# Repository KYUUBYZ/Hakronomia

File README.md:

# Hakronomia

<!--START_SECTION:BOM-TABLE-->
| Item | Qty | Supplier | Cost/item | Total Cost | link |
| --- | --- | --- | --- | --- | --- |
| 0.1uF | 6 | Unikeyic | $0.08 | $0.48 | [Link](https://www.unikeyic.com/products/ceramic-capacitors/gcd21br72a104ka01l/10036938.html?sku=1003001027405269) |
| 2.2nF | 2 | Unikeyic | $0.05 | $0.10 | [Link](https://www.unikeyic.com/products/ceramic-capacitors/gcm2165c2a222ja16d/5775567.html?sku=1003001445194783) |
| 10nF | 6 | Unikeyic | $0.01 | $0.06 | [Link](https://www.unikeyic.com/products/ceramic-capacitors/cc0805jrx7r9bb103/17962920.html?sku=1003001445184833) |
| 2.2uF | 2 | Unikeyic | $0.05 | $0.10 | [Link](https://www.unikeyic.com/products/ceramic-capacitors/cga4j3x7r1c225kt0y0n/8873476.html?sku=1003001017784221) |
| 10uF | 4 | Unikeyic | $0.08 | $0.32 | [Link](https://www.unikeyic.com/products/ceramic-capacitors/c2012x7r0j106k125ab/17422021.html?sku=1003001013214412) |
| AudioJack5 | 1 | Futuranet | $0.30 | $0.30 | [Link](https://futuranet.it/prodotto/presa-jack-stereo-35-mm-da-circuito-stampato/) |
| 330R | 12 | Unikeyic | $0.01 | $0.12 | [Link](https://www.unikeyic.com/products/surface-mount-resistors/rc0805fr-07330rl/4454264.html?sku=1003001443534963) |
| 4.7k | 2 | Unikeyic | $0.01 | $0.02 | [Link](https://www.unikeyic.com/products/surface-mount-resistors/rc0805fr-7w4k7l/3329266.html?sku=1003001021096266) |
| 75k | 1 | Unikeyic | $0.00 | $0.00 | [Link](https://www.unikeyic.com/products/surface-mount-resistors/wr08x753-jtl/28917829.html?sku=1003001442043903) |
| 10k | 2 | Unikeyic | $0.00 | $0.00 | [Link](https://www.unikeyic.com/products/surface-mount-resistors/0805w8f1002t5e/33861683.html?sku=1003001012328856) |
| 470R | 2 | Unikeyic | $0.00 | $0.00 | [Link](https://www.unikeyic.com/products/surface-mount-resistors/0805w8f4700t5e/27378691.html?sku=1003001012328951) |
| 0R | 1 | Unikeyic | $0.01 | $0.01 | [Link](https://www.unikeyic.com/products/surface-mount-resistors/rtt050000ftp/30082103.html?sku=1003001013772933) |
| RP2040-Zero | 1 | Futuranet | $6.61 | $6.61 | [Link](https://futuranet.it/prodotto/scheda-di-sviluppo-mini-basata-su-rp2040/) |
| RotaryEncoder_Switch_MP | 3 | Unikeyic | $1.49 | $4.47 | [Link](https://www.unikeyic.com/products/encoders-and-decoders/ec11e15244g1/24342867.html?sku=1003001012811431) |
| ER_OLEDM0.91_1x-I2C | 1 | Futuranet | $6.50 | $6.50 | [Link](https://futuranet.it/prodotto/display-oled-i2c-091-128x32-pixel/) |
| MPR121QR2 | 1 | Unikeyic | $1.61 | $1.61 | [Link](https://www.unikeyic.com/products/other-interface/mpr121qr2/11118659.html?sku=1003001027325782) |
| PCM5102A | 1 | Unikeyic | $1.31 | $1.31 | [Link](https://www.unikeyic.com/products/adc-dac-specialized/pcm5102apwr/33225117.html?sku=1003001444976630) |
| Estimated total shipping | 1 |  |  | $7.50 |  |
<!--END_SECTION:BOM-TABLE-->
# HOW TO INSTALL THE FIRMWARE (Hakronomia.py):

1)    Connect your RP2040-ZERO to your PC using a data transfer cable while pressing BOOT 

2)    Install/Copy the "adafruit-ciruitpython-waveshare" file i put in this folder ON the RP2040-ZERO.

3)    you should see file be downloaded on your microcontroller.

4)    From CircuitPython libraries bundle, copy "adafruit_mpr121, adafruit_displayio_ssd1306, adafruit_display_text, adafruit_bus_device" on the rp2040-zero.

5)    Copy Hakronomia.py on the rp2040-zero

# What is Hakronomia?
Hakronomia, Midi keyboard, it's a Piano style keyboard an it has 12 exposed copper plates keys, plus 3 rotary encoder, a 0.91 inch screen, a switch and a 3.5mm AudioJack.
It uses a MPR121QR2 ( The MPR121QR2 is a Capacitive Touch Sensor Controller )  and the PCM5102A ( DAC Chip (Digital-to-Analog Converter ).

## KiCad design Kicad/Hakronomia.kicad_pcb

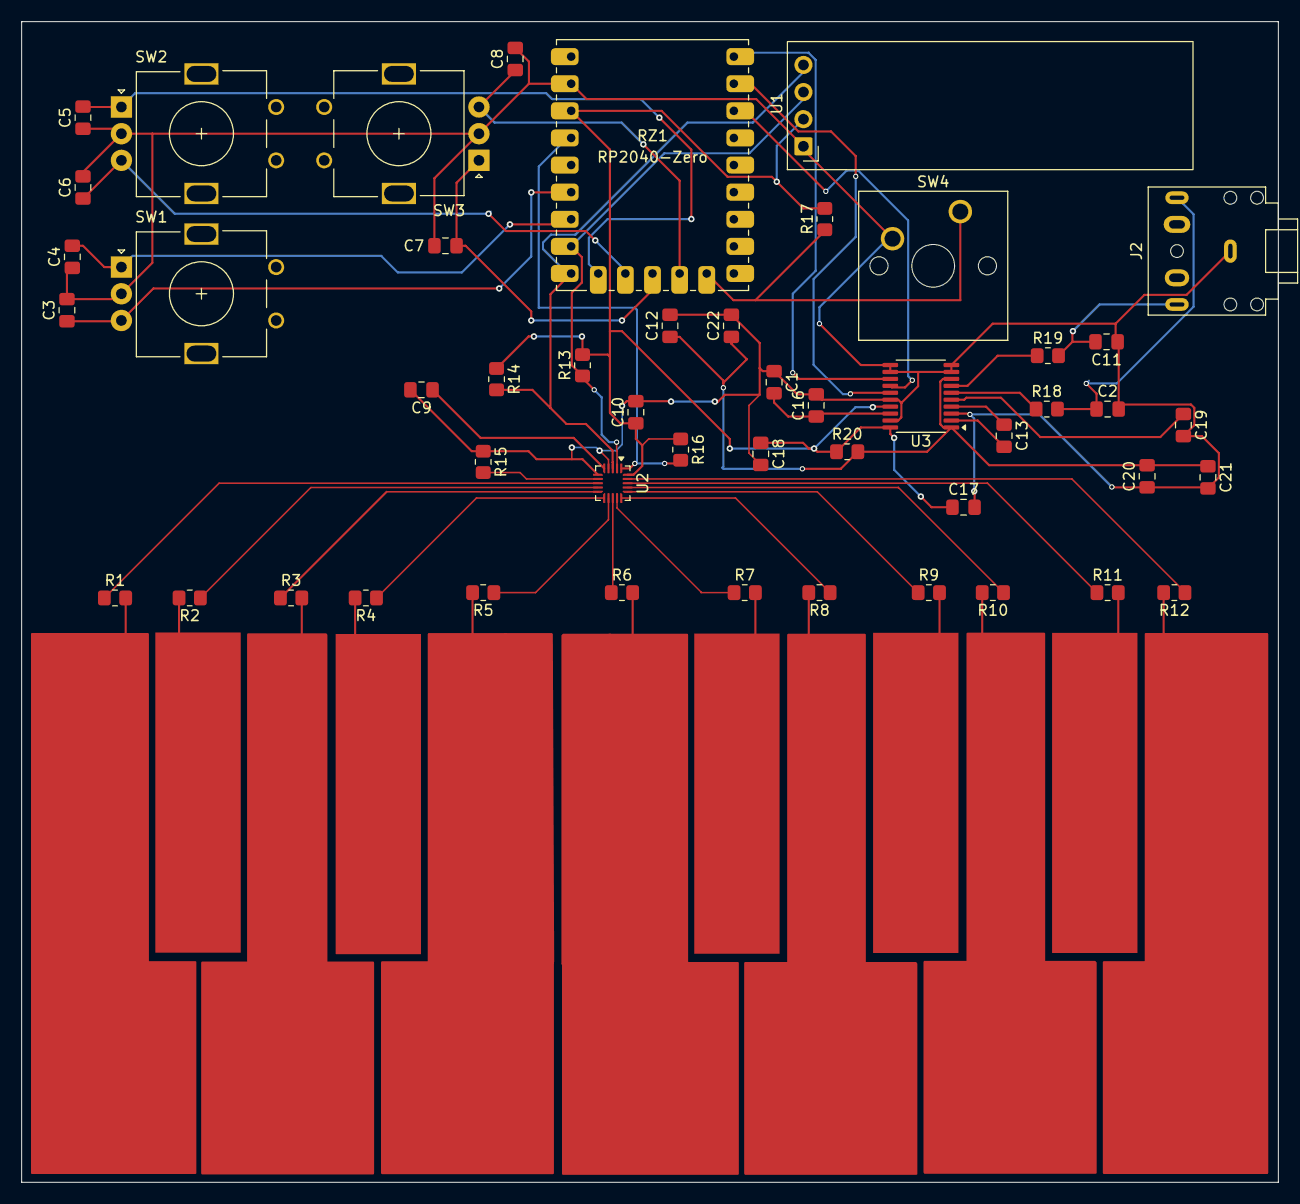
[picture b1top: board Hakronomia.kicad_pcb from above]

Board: 2 copper layers, 117.8 x 108.8 mm, 50 parts (0 on the bottom side), 50 nets.

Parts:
C1, C9, C10, C12, C18, C20: 0.1uF; C_0805_2012Metric_Pad1.18x1.45mm_HandSolder
C2, C11: 2.2nF; C_0805_2012Metric_Pad1.18x1.45mm_HandSolder
C3, C4, C5, C6, C7, C8: 10nF; C_0805_2012Metric_Pad1.18x1.45mm_HandSolder
C13, C19: 2.2uF; C_0805_2012Metric_Pad1.18x1.45mm_HandSolder
C16, C17, C21, C22: 10uF; C_0805_2012Metric_Pad1.18x1.45mm_HandSolder
J1: Conn_01x12_Pin; Hakronomia Pads
J2: AudioJack5; Jack_3.5mm_CUI_SJ1-3525N_Horizontal
R1, R2, R3, R4, R5, R6, R7, R8, R9, R10, R11, R12: 330R; R_0805_2012Metric_Pad1.20x1.40mm_HandSolder
R13, R14: 4.7k; R_0805_2012Metric_Pad1.20x1.40mm_HandSolder
R15: 75k; R_0805_2012Metric_Pad1.20x1.40mm_HandSolder
R16, R17: 10k; R_0805_2012Metric_Pad1.20x1.40mm_HandSolder
R18, R19: 470R; R_0805_2012Metric_Pad1.20x1.40mm_HandSolder
R20: 0R; R_0805_2012Metric_Pad1.20x1.40mm_HandSolder
RZ1: RP2040-Zero
SW1, SW2, SW3: RotaryEncoder_Switch_MP; RotaryEncoder_Alps_EC11E_Vertical_H20mm
SW4: SW_Push; SW_Cherry_MX_1.25u_PCB
U1: ER_OLEDM0.91_1x-I2C
U2: MPR121QR2; UQFN-20_3x3mm_P0.4mm
U3: PCM5102A; TSSOP-20_4.4x6.5mm_P0.65mm

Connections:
AGND: C1.1, C2.2, C3.2, C4.1, C5.1, C6.2, C7.1, C8.2, C9.2, C10.2, C11.1, C12.2, C16.2, C17.2, C18.2, C19.2, C20.1, C21.2, C22.2, J2.S, R15.1, RZ1.22 (GND), SW1.C, SW2.C, SW3.C, SW4.2, U1.1 (GND), U2.4 (ADDR), U2.6 (VSS), U3.3 (CPGND), U3.9 (AGND), U3.10 (DEMP), U3.11 (FLT), U3.12 (SCK), U3.16 (FMT), U3.19 (DGND)
AVDD: C12.1, C20.2, C21.1, C22.1, R20.2, U3.1 (CPVDD), U3.8 (AVDD)
BCK: RZ1.1 (GP0), U3.13 (BCK)
DIN: RZ1.3 (GP2), U3.14 (DIN)
DVDD: C10.1, C17.1, C18.1, R13.2, R14.1, R16.1, R17.2, R20.1, RZ1.21 (3V3), U1.2 (VCC), U2.20 (VDD), U3.17 (XSMT), U3.20 (DVDD)
ENC-A0: C4.2, RZ1.17 (GP26), SW1.A
ENC-A1: C5.2, RZ1.14 (GP13), SW2.A
ENC-A2: C7.2, RZ1.12 (GP11), SW3.A
ENC-B0: C3.1, RZ1.18 (GP27), SW1.B
ENC-B1: C6.1, RZ1.13 (GP12), SW2.B
ENC-B2: C8.1, RZ1.11 (GP10), SW3.B
LRCK: RZ1.2 (GP1), U3.15 (LRCK)
MPR-IRQ: R16.2, RZ1.20 (GP29), U2.1 (~IRQ)
unnamed: C2.1, J2.T, R18.2
unnamed: C11.2, J2.R, R19.2
unnamed: J1.1, R1.2
unnamed: J1.2, R2.2
unnamed: J1.3, R3.2
unnamed: J1.4, R4.2
unnamed: J1.5, R5.2
unnamed: J1.6, R6.2
unnamed: J1.7, R7.2
unnamed: J1.8, R8.2
unnamed: J1.9, R9.2
unnamed: J1.10, R10.2
unnamed: J1.11, R11.2
unnamed: J1.12, R12.2
unnamed: R15.2, U2.7 (REXT)
unnamed: C9.1, U2.5 (VREG)
unnamed: C13.1, U3.4 (CAPM)
unnamed: C13.2, U3.2 (CAPP)
unnamed: C1.2, C16.1, U3.18 (LDOO)
unnamed: R18.1, U3.6 (OUTL)
unnamed: R19.1, U3.7 (OUTR)
SCL: R13.1, RZ1.16 (GP15), U1.3 (SCL), U2.2 (SCL)
SDA: R14.2, RZ1.15 (GP14), U1.4 (SDA), U2.3 (SDA)
SWITCH-0: R17.1, RZ1.10 (GP9), SW4.1
Touch1: R1.1, U2.8 (ELE0)
Touch2: R2.1, U2.9 (ELE1)
Touch3: R3.1, U2.10 (ELE2)
Touch4: R4.1, U2.11 (ELE3)
Touch5: R5.1, U2.12 (LED0/ELE4)
Touch6: R6.1, U2.13 (LED1/ELE5)
Touch7: R7.1, U2.14 (LED2/ELE6)
Touch8: R8.1, U2.15 (LED3/ELE7)
Touch9: R9.1, U2.16 (LED4/ELE8)
Touch10: R10.1, U2.17 (LED5/ELE9)
Touch11: R11.1, U2.18 (LED6/ELE10)
Touch12: R12.1, U2.19 (LED7/ELE11)
VNEG: C19.1, U3.5 (VNEG)

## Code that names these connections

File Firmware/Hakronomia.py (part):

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LONG_MS = 800

# I2S to PCM5102A (BCK and LRCK must be consecutive)
PIN_BCK, PIN_LRCK, PIN_DIN = board.GP0, board.GP1, board.GP2
# I2C addresses (MPR121 to 0x5A, Oled to 0x3C)
PIN_SDA, PIN_SCL, = board.GP14, board.GP15

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]

# ============================== AUDIO ===============================
audio = audiobusio.I2SOut(bit_clock=PIN_BCK, word_select=PIN_LRCK, data=PIN_DIN)
mixer = audiomixer.Mixer(voice_count=1, sample_rate=SAMPLE_RATE,
                         channel_count=1, bits_per_sample=16,
                         samples_signed=True, buffer_size=2948)
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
